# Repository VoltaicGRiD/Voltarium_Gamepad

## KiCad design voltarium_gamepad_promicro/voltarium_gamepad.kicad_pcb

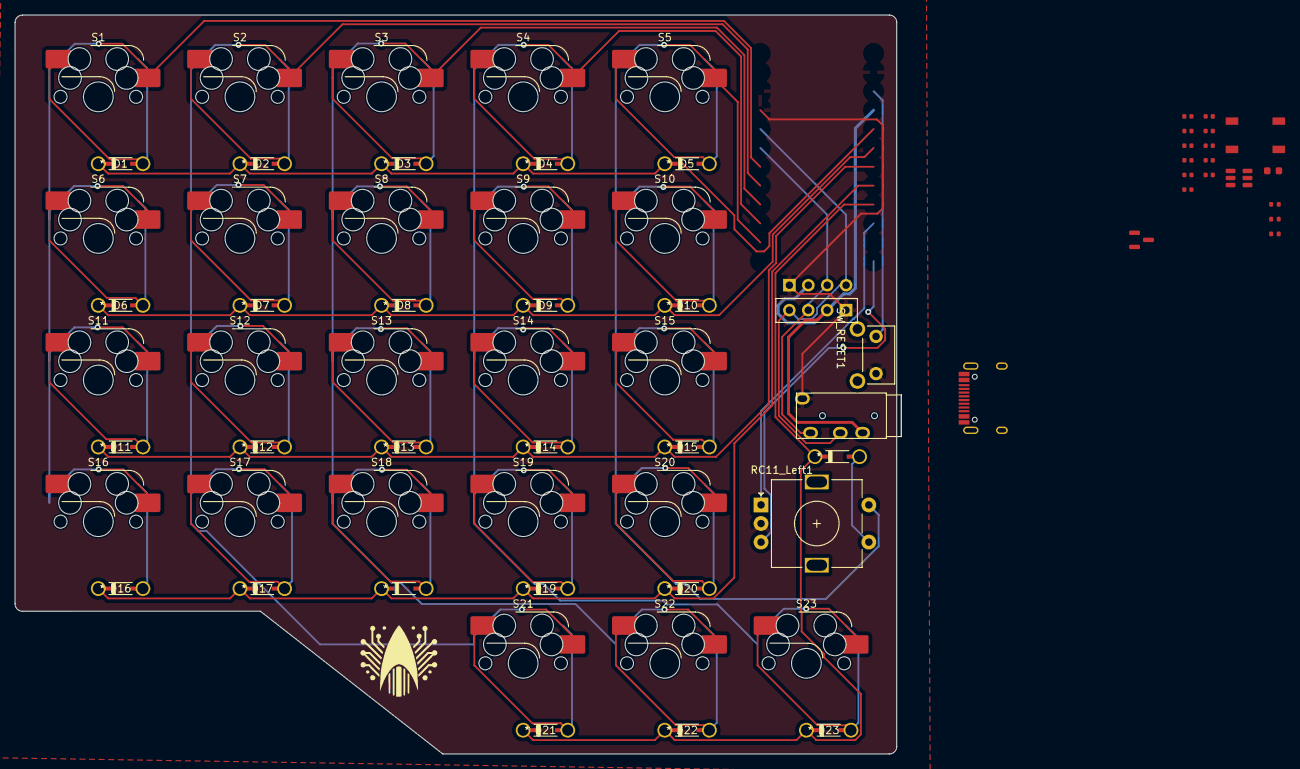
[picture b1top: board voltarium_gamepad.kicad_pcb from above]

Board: 2 copper layers, 118.6 x 99.4 mm, 71 parts (1 on the bottom side), 46 nets.

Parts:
C1, C2, C3, C5, C8: 100nF; Capacitor_0402
C4, C9: 4.7uF; Capacitor_0402
C6: 10nF; Capacitor_0402
C7, C10, C11: 1uF; Capacitor_0402
D1, D2, D3, D4, D5, D6, D7, D8, D9, D10, D11, D12, D13, D14, D15, D16, D17, D18, D19, D20, D21, D22, D23, D24: 1N4148; SOD123_DIO-L With THs
F1: 500mA; Fuse_0603
J1, J2: OLED_128x32
J3: USB_C; USB_C_HRO_TYPE-C-31-M-12
R1: 10k; Resistor_0402
R2, R3: 5.1k; Resistor_0402
RC11_Left1: RotaryEncoder_Switch; RotaryEncoder_Alps_EC11E-Switch_Vertical_H20mm
S1, S2, S3, S4, S5, S6, S7, S8, S9, S10, S11, S12, S13, S14, S15, S16, S17, S18, S19, S20, S21, S22, S23: Keyswitch; Hotswap_MX_Plated_1.00u Reversible - Same Side
SW1: SW_Push; Button_TL3342
SW_RESET1: Switch; SW_SKHLLCA010
U3: TRRS; TRRS_PJ-320A
U4: USBLC6-2SC6; ESD_SOT-23-6
U5: XC6206; Voltage_SOT-23

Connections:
+3.3V: C2.2, C3.2, C4.2, C5.2, C6.2, C7.2, C8.2, C9.2, C11.1, SW1.1, U5.2 (VO)
+5V: C10.1, F1.2, U5.3 (VI)
/BOOT0: R1.2, SW1.2
/USB_D+: J3.A6 (D+), J3.B6 (D+), U4.6 (I/O1)
/USB_D-: J3.A7 (D-), J3.B7 (D-), U4.4 (I/O2)
C1: S1.1, S6.1, S11.1, S16.1
C2: S2.1, S7.1, S12.1, S17.1, S21.1
C3: S3.1, S8.1, S13.1, S18.1, S22.1
C4: S4.1, S9.1, S14.1, S19.1, S23.1
C5: RC11_Left1.S2, S5.1, S10.1, S15.1, S20.1
GND: C1.2, C2.1, C3.1, C4.1, C5.1, C6.1, C7.1, C8.1, C9.1, C10.2, C11.2, J1.1 (GND), J2.1 (GND), J3.A1 (GND), J3.A12 (GND), J3.B1 (GND), J3.B12 (GND), J3.S1 (SHIELD), R1.1, R2.2, R3.2, RC11_Left1.C, SW_RESET1.1, U3.1 (SLEEVE), U4.2 (GND), U5.1 (GND)
unnamed: D1.2 (A), S1.2
unnamed: D2.2 (A), S2.2
unnamed: D3.2 (A), S3.2
unnamed: D4.2 (A), S4.2
unnamed: D5.2 (A), S5.2
unnamed: D6.2 (A), S6.2
unnamed: D7.2 (A), S7.2
unnamed: D8.2 (A), S8.2
unnamed: D9.2 (A), S9.2
unnamed: D10.2 (A), S10.2
unnamed: D11.2 (A), S11.2
unnamed: D12.2 (A), S12.2
unnamed: D13.2 (A), S13.2
unnamed: D14.2 (A), S14.2
unnamed: D15.2 (A), S15.2
unnamed: D16.2 (A), S16.2
unnamed: D17.2 (A), S17.2
unnamed: D18.2 (A), S18.2
unnamed: D19.2 (A), S19.2
unnamed: D20.2 (A), S20.2
unnamed: D21.2 (A), S21.2
unnamed: D22.2 (A), S22.2
unnamed: D23.2 (A), S23.2
unnamed: D24.2 (A), RC11_Left1.S1
unnamed: J3.A5 (CC1), R2.1
unnamed: J3.B5 (CC2), R3.1
R1: D1.1 (K), D2.1 (K), D3.1 (K), D4.1 (K), D5.1 (K)
R2: D6.1 (K), D7.1 (K), D8.1 (K), D9.1 (K), D10.1 (K)
R3: D11.1 (K), D12.1 (K), D13.1 (K), D14.1 (K), D15.1 (K)
R4: D16.1 (K), D17.1 (K), D18.1 (K), D19.1 (K), D20.1 (K)
R5: D21.1 (K), D22.1 (K), D23.1 (K), D24.1 (K)
SCL: J1.3 (SCL), J2.3 (SCL), U3.2 (TIP)
SDA: J1.4 (SDA), J2.4 (SDA), U3.3 (RING1)
VBUS: F1.1, J3.A4 (VBUS), J3.A9 (VBUS), J3.B4 (VBUS), J3.B9 (VBUS), U4.5 (VBUS)
VCC: J1.2 (VCC), J2.2 (VCC), U3.4 (RING2)

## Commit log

2024-09-25 Voltarium Gamepad w/ Scottokeebs Modules
2024-09-25 Moved pro-micro version to its own folder
